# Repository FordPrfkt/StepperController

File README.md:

# StepperController
Stepper Motor Controller using TMC2660

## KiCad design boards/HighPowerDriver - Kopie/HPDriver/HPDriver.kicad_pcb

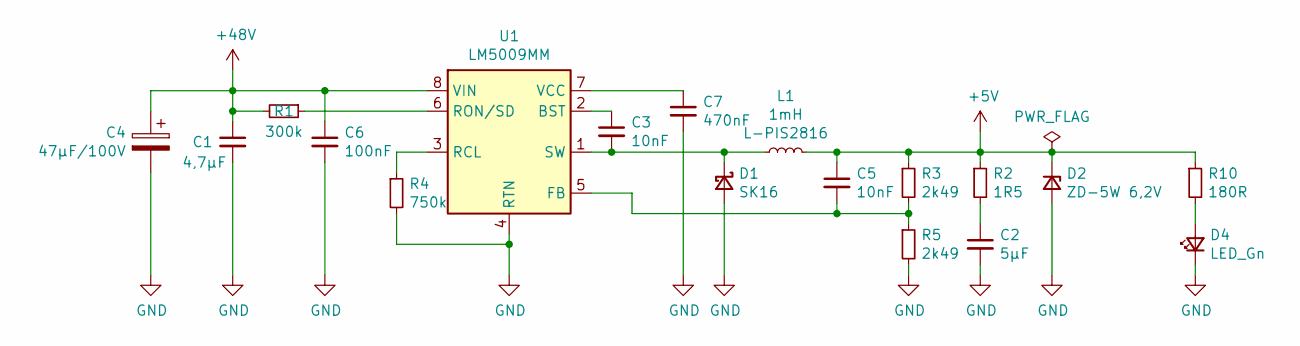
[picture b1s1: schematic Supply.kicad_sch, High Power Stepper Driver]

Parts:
C1: 4,7µF; C_1210_3225Metric
C2: 5µF; C_1210_3225Metric
C3, C5: 10nF; C_0805_2012Metric
C4: 47µF/100V; CP_Elec_8x10
C6: 100nF; C_0805_2012Metric
C7: 470nF; C_0805_2012Metric
D1: SK16; D_SMA
D2: ZD-5W 6,2V; D_SMB
D4: LED_Gn; LED_0805_2012Metric
L1: 1mH; L_7.3x7.3_H4.5
R1: 300k; R_0805_2012Metric
R2: 1R5; R_0805_2012Metric
R3, R5: 2k49; R_0805_2012Metric
R4: 750k; R_0805_2012Metric
R10: 180R; R_0805_2012Metric
U1: LM5009MM; MSOP-8_3x3mm_P0.65mm

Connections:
+5V: C5.1, D2.1 (K), L1.2, R2.1, R3.1, R10.1; also elsewhere on the board
+48V: C1.1, C4.1, C6.1, R1.2, U1.8 (VIN); also elsewhere on the board
GND: C1.2, C2.2, C4.2, C6.2, C7.2, D1.2 (A), D2.2 (A), D4.1 (K), R4.2, R5.2, U1.4 (RTN); also elsewhere on the board
unnamed: C2.1, R2.2
unnamed: C3.1, U1.2 (BST)
unnamed: C3.2, D1.1 (K), L1.1, U1.1 (SW)
unnamed: C5.2, R3.2, R5.1, U1.5 (FB)
unnamed: C7.1, U1.7 (VCC)
unnamed: D4.2 (A), R10.2
unnamed: R1.1, U1.6 (RON/SD)
unnamed: R4.1, U1.3 (RCL)

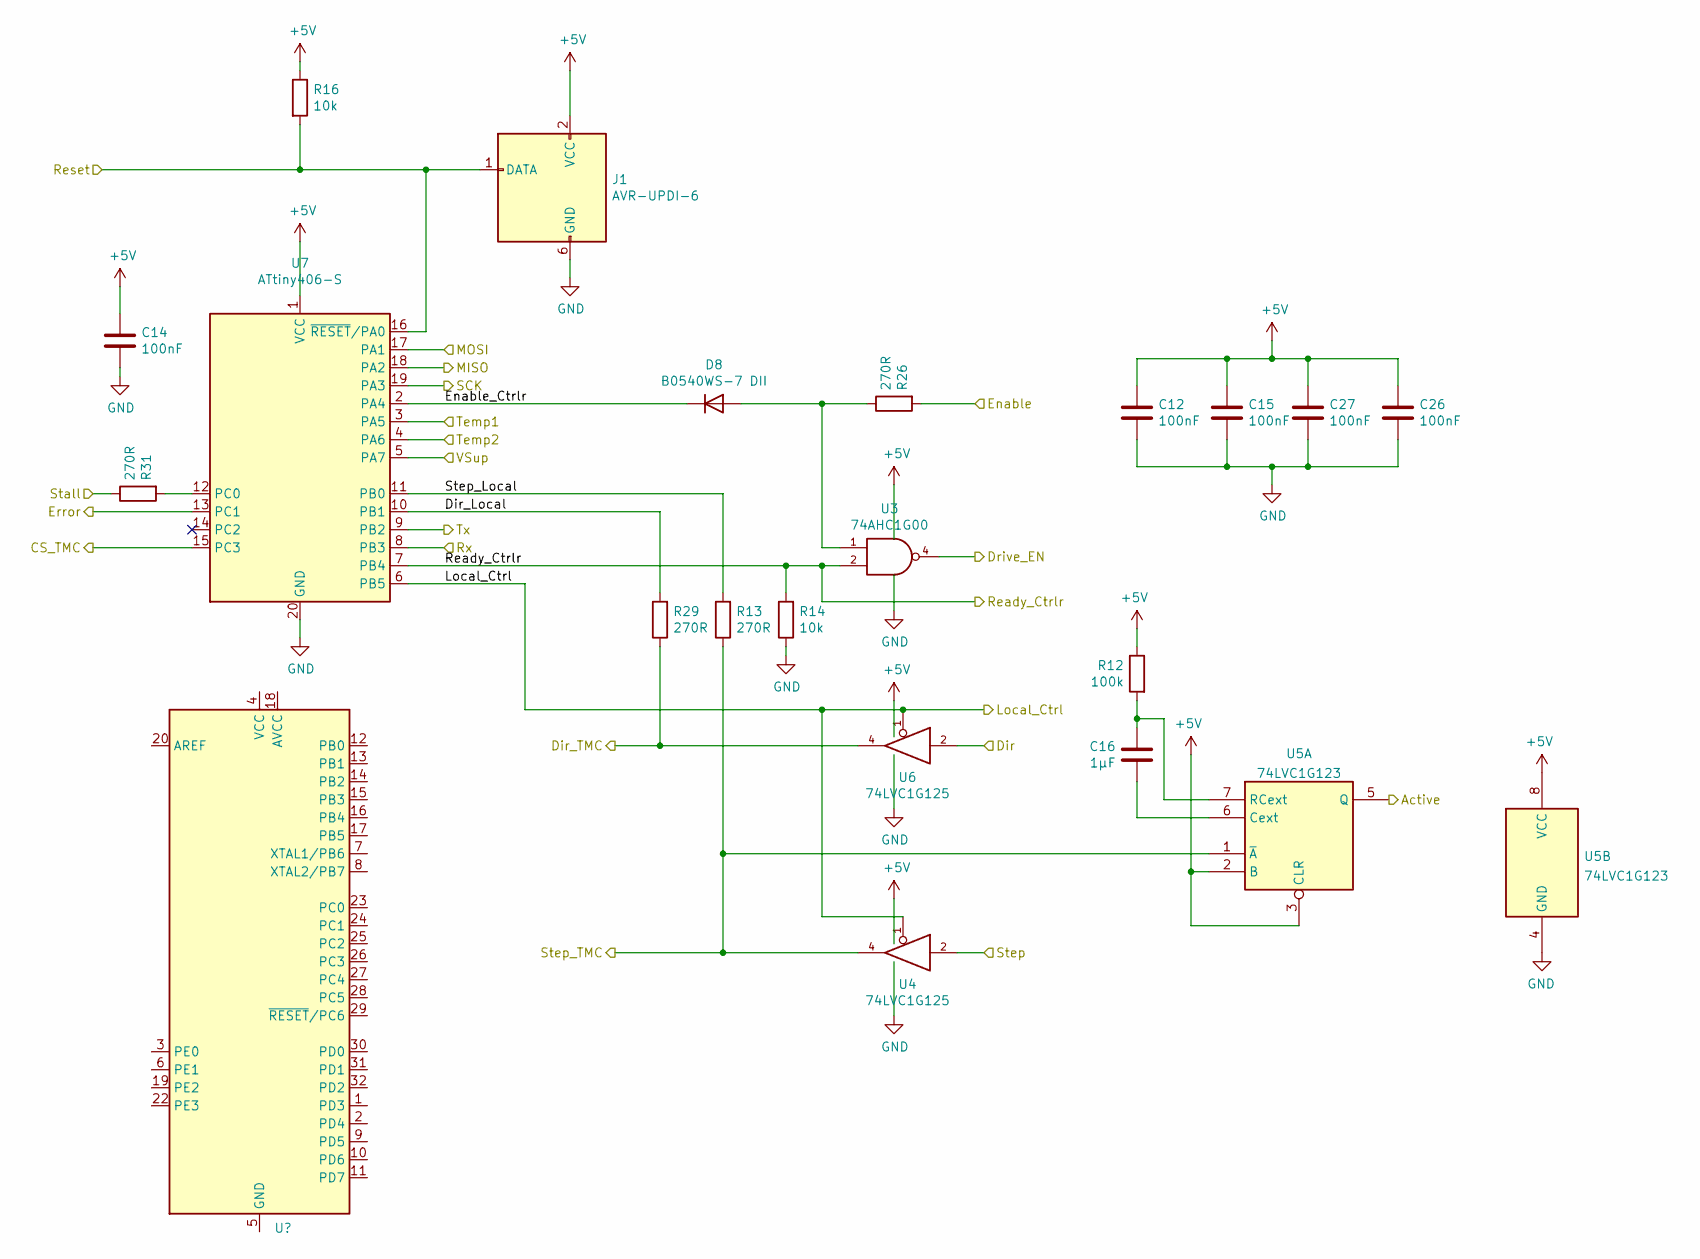
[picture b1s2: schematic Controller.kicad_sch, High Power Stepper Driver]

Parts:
C12, C14, C15, C26, C27: 100nF; C_0805_2012Metric
C16: 1µF; C_0805_2012Metric
D8: B0540WS-7 DII; D_SOD-323
J1: AVR-UPDI-6; IDC-Header_2x03_P2.54mm_Vertical
R12: 100k; R_0805_2012Metric
R13, R26, R29, R31: 270R; R_0805_2012Metric
R14, R16: 10k; R_0805_2012Metric
U3: 74AHC1G00; SOT-23-5
U4, U6: 74LVC1G125; SOT-23-5
U5: 74LVC1G123; VSSOP-8_3.0x3.0mm_P0.65mm
U7: ATtiny406-S; SOIC-20W_7.5x12.8mm_P1.27mm

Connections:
+5V: C12.1, C14.1, C15.1, C26.1, C27.1, J1.2 (VCC), R12.1, R16.1, U3.5 (VCC), U4.5 (VCC), U5.2 (B), U5.3 (CLR), U5.8 (VCC), U6.5 (VCC), U7.1 (VCC); also elsewhere on the board
/Connector/Active: U5.5 (Q); also elsewhere on the board
/Connector/Dir: U6.2; also elsewhere on the board
/Connector/Enable: R26.2; also elsewhere on the board
/Connector/Error: U7.13 (PC1); also elsewhere on the board
/Connector/Reset: J1.1 (DATA), R16.2, U7.16 (~RESET/PA0); also elsewhere on the board
/Connector/Rx: U7.8 (PB3); also elsewhere on the board
/Connector/Stall: R31.1; also elsewhere on the board
/Connector/Step: U4.2; also elsewhere on the board
/Connector/Tx: U7.9 (PB2); also elsewhere on the board
/Connector/VSup: U7.5 (PA7); also elsewhere on the board
/Controller/CS_TMC: U7.15 (PC3); also elsewhere on the board
/Controller/Dir_Local: R29.2, U7.10 (PB1)
/Controller/Dir_TMC: R29.1, U6.4; also elsewhere on the board
/Controller/Drive_EN: U3.4; also elsewhere on the board
/Controller/Enable_Ctrlr: D8.1 (K), U7.2 (PA4)
/Controller/Local_Ctrl: U4.1, U6.1, U7.6 (PB5); also elsewhere on the board
/Controller/MISO: U7.18 (PA2); also elsewhere on the board
/Controller/MOSI: U7.17 (PA1); also elsewhere on the board
/Controller/Ready_Ctrlr: R14.2, U3.2, U7.7 (PB4); also elsewhere on the board
/Controller/SCK: U7.19 (PA3); also elsewhere on the board
/Controller/Step_Local: R13.2, U7.11 (PB0)
/Controller/Step_TMC: R13.1, U4.4, U5.1 (~A); also elsewhere on the board
/Controller/Temp1: U7.3 (PA5); also elsewhere on the board
/Controller/Temp2: U7.4 (PA6); also elsewhere on the board
GND: C12.2, C14.2, C15.2, C26.2, C27.2, J1.6 (GND), R14.1, U3.3 (GND), U4.3 (GND), U5.4 (GND), U6.3 (GND), U7.20 (GND); also elsewhere on the board
unnamed: C16.1, U5.6 (Cext)
unnamed: C16.2, R12.2, U5.7 (RCext)
unnamed: D8.2 (A), R26.1, U3.1
unnamed: R31.2, U7.12 (PC0)

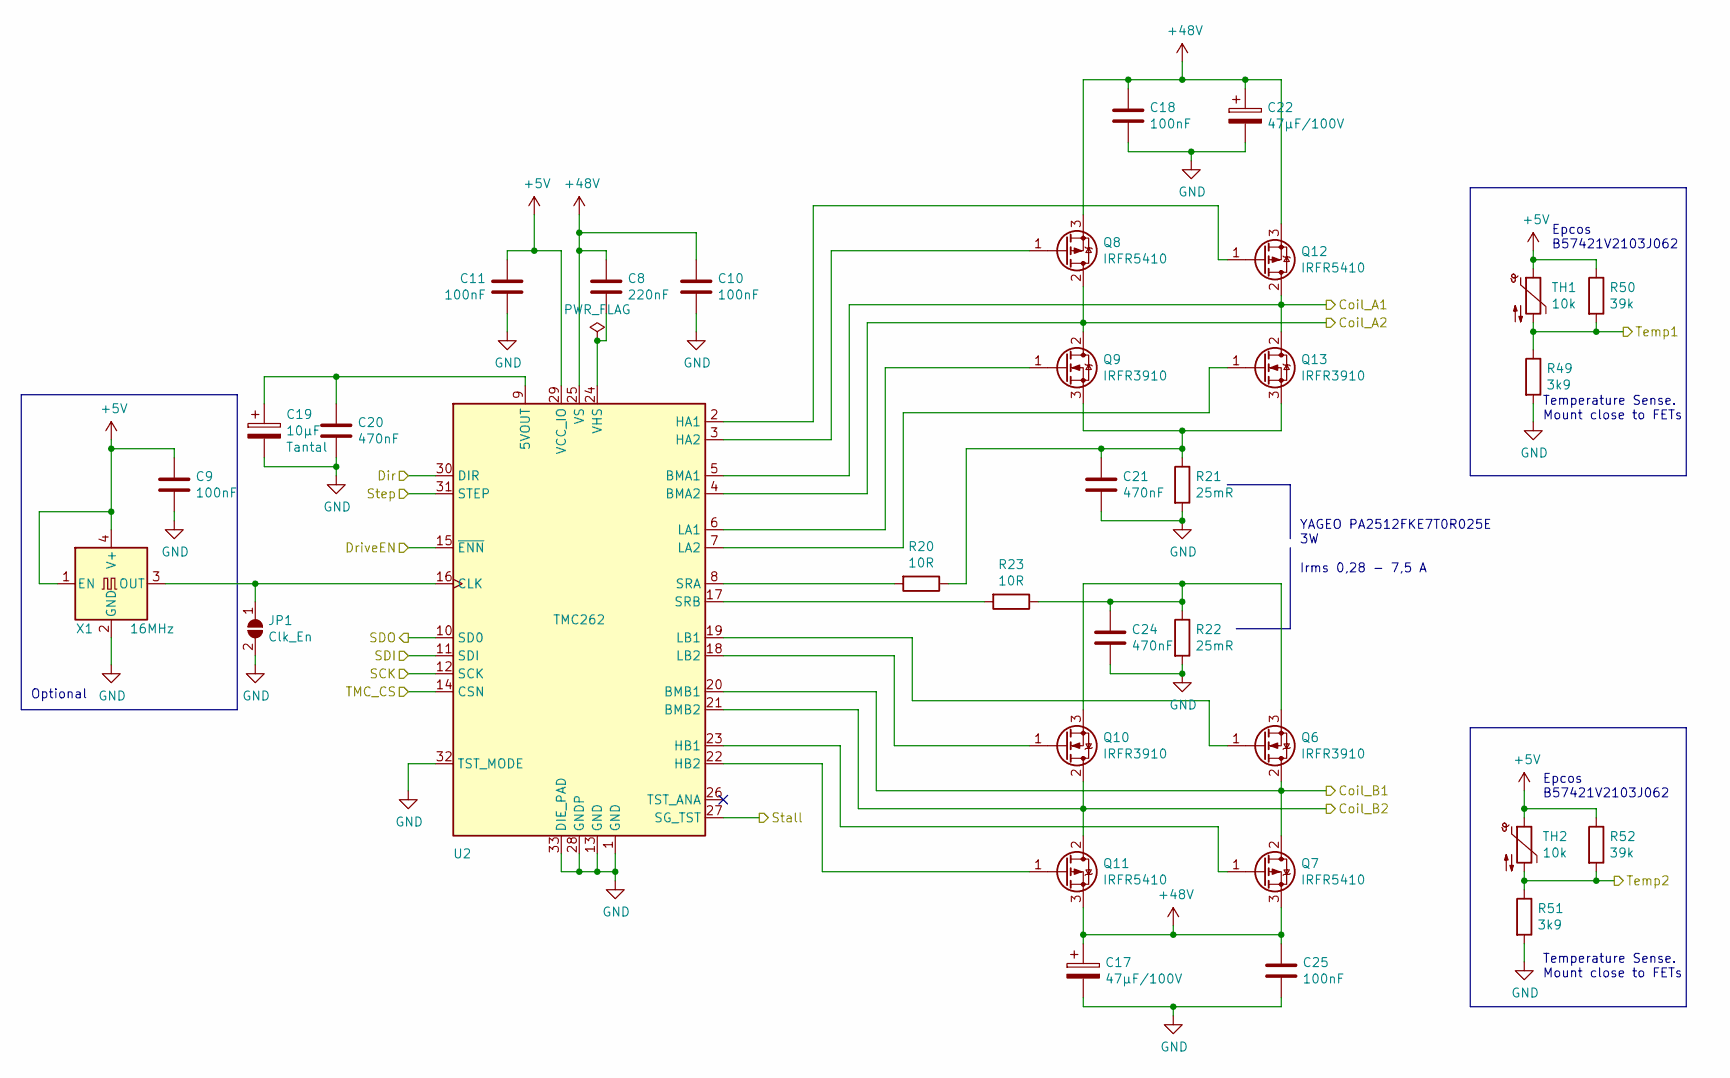
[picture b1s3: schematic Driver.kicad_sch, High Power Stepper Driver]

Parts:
C8: 220nF; C_0805_2012Metric
C9, C10, C11, C18, C25: 100nF; C_0805_2012Metric
C17, C22: 47µF/100V; CP_Elec_10x10
C19: 10µF; CP_EIA-3528-21_Kemet-B
C20, C21, C24: 470nF; C_0805_2012Metric
JP1: Clk_En; SolderJumper-2_P1.3mm_Open_TrianglePad1.0x1.5mm
Q6, Q9, Q10, Q13: IRFR3910; TO-252-2
Q7, Q8, Q11, Q12: IRFR5410; TO-252-2
R20, R23: 10R; R_0805_2012Metric
R21, R22: 25mR; R_2512_6332Metric
R49, R51: 3k9; R_0805_2012Metric
R50, R52: 39k; R_0805_2012Metric
TH1, TH2: 10k; R_0805_2012Metric
U2: TMC262; QFN-32-1EP_5x5mm_P0.5mm_EP3.45x3.45mm
X1: 16MHz; Oscillator_SMD_EuroQuartz_XO53-4Pin_5.0x3.2mm_HandSoldering

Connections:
+5V: C9.1, C11.1, R50.1, R52.1, TH1.1, TH2.1, U2.29 (VCC_IO), X1.1 (EN), X1.4 (V+); also elsewhere on the board
+48V: C8.1, C10.1, C17.1, C18.1, C22.1, C25.1, Q7.3 (S), Q8.3 (S), Q11.3 (S), Q12.3 (S), U2.25 (VS); also elsewhere on the board
/Connector/Coil_A1: Q12.2 (D), Q13.2 (D), U2.5 (BMA1); also elsewhere on the board
/Connector/Coil_A2: Q8.2 (D), Q9.2 (D), U2.4 (BMA2); also elsewhere on the board
/Connector/Coil_B1: Q6.2 (D), Q7.2 (D), U2.20 (BMB1); also elsewhere on the board
/Connector/Coil_B2: Q10.2 (D), Q11.2 (D), U2.21 (BMB2); also elsewhere on the board
/Connector/Stall: U2.27 (SG_TST); also elsewhere on the board
/Controller/CS_TMC: U2.14 (CSN); also elsewhere on the board
/Controller/Dir_TMC: U2.30 (DIR); also elsewhere on the board
/Controller/Drive_EN: U2.15 (~ENN); also elsewhere on the board
/Controller/MISO: U2.11 (SDI); also elsewhere on the board
/Controller/MOSI: U2.10 (SD0); also elsewhere on the board
/Controller/SCK: U2.12 (SCK); also elsewhere on the board
/Controller/Step_TMC: U2.31 (STEP); also elsewhere on the board
/Controller/Temp1: R49.1, R50.2, TH1.2; also elsewhere on the board
/Controller/Temp2: R51.1, R52.2, TH2.2; also elsewhere on the board
GND: C9.2, C10.2, C11.2, C17.2, C18.2, C19.2, C20.2, C21.2, C22.2, C24.2, C25.2, JP1.2 (B), R21.2, R22.2, R49.2, R51.2, U2.1 (GND), U2.13 (GND), U2.28 (GNDP), U2.32 (TST_MODE), U2.33 (DIE_PAD), X1.2 (GND); also elsewhere on the board
unnamed: C8.2, U2.24 (VHS)
unnamed: C19.1, C20.1, U2.9 (5VOUT)
unnamed: C21.1, Q9.3 (S), Q13.3 (S), R20.1, R21.1
unnamed: C24.1, Q6.3 (S), Q10.3 (S), R22.1, R23.1
unnamed: JP1.1 (A), U2.16 (CLK), X1.3 (OUT)
unnamed: Q6.1 (G), U2.19 (LB1)
unnamed: Q7.1 (G), U2.23 (HB1)
unnamed: Q8.1 (G), U2.3 (HA2)
unnamed: Q9.1 (G), U2.6 (LA1)
unnamed: Q10.1 (G), U2.18 (LB2)
unnamed: Q11.1 (G), U2.22 (HB2)
unnamed: Q12.1 (G), U2.2 (HA1)
unnamed: Q13.1 (G), U2.7 (LA2)
unnamed: R20.2, U2.8 (SRA)
unnamed: R23.2, U2.17 (SRB)

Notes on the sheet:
YAGEO PA2512FKE7T0R025E 3W Irms 0,28 - 7,5 A
Epcos B57421V2103J062
Temperature Sense. Mount close to FETs
Optional

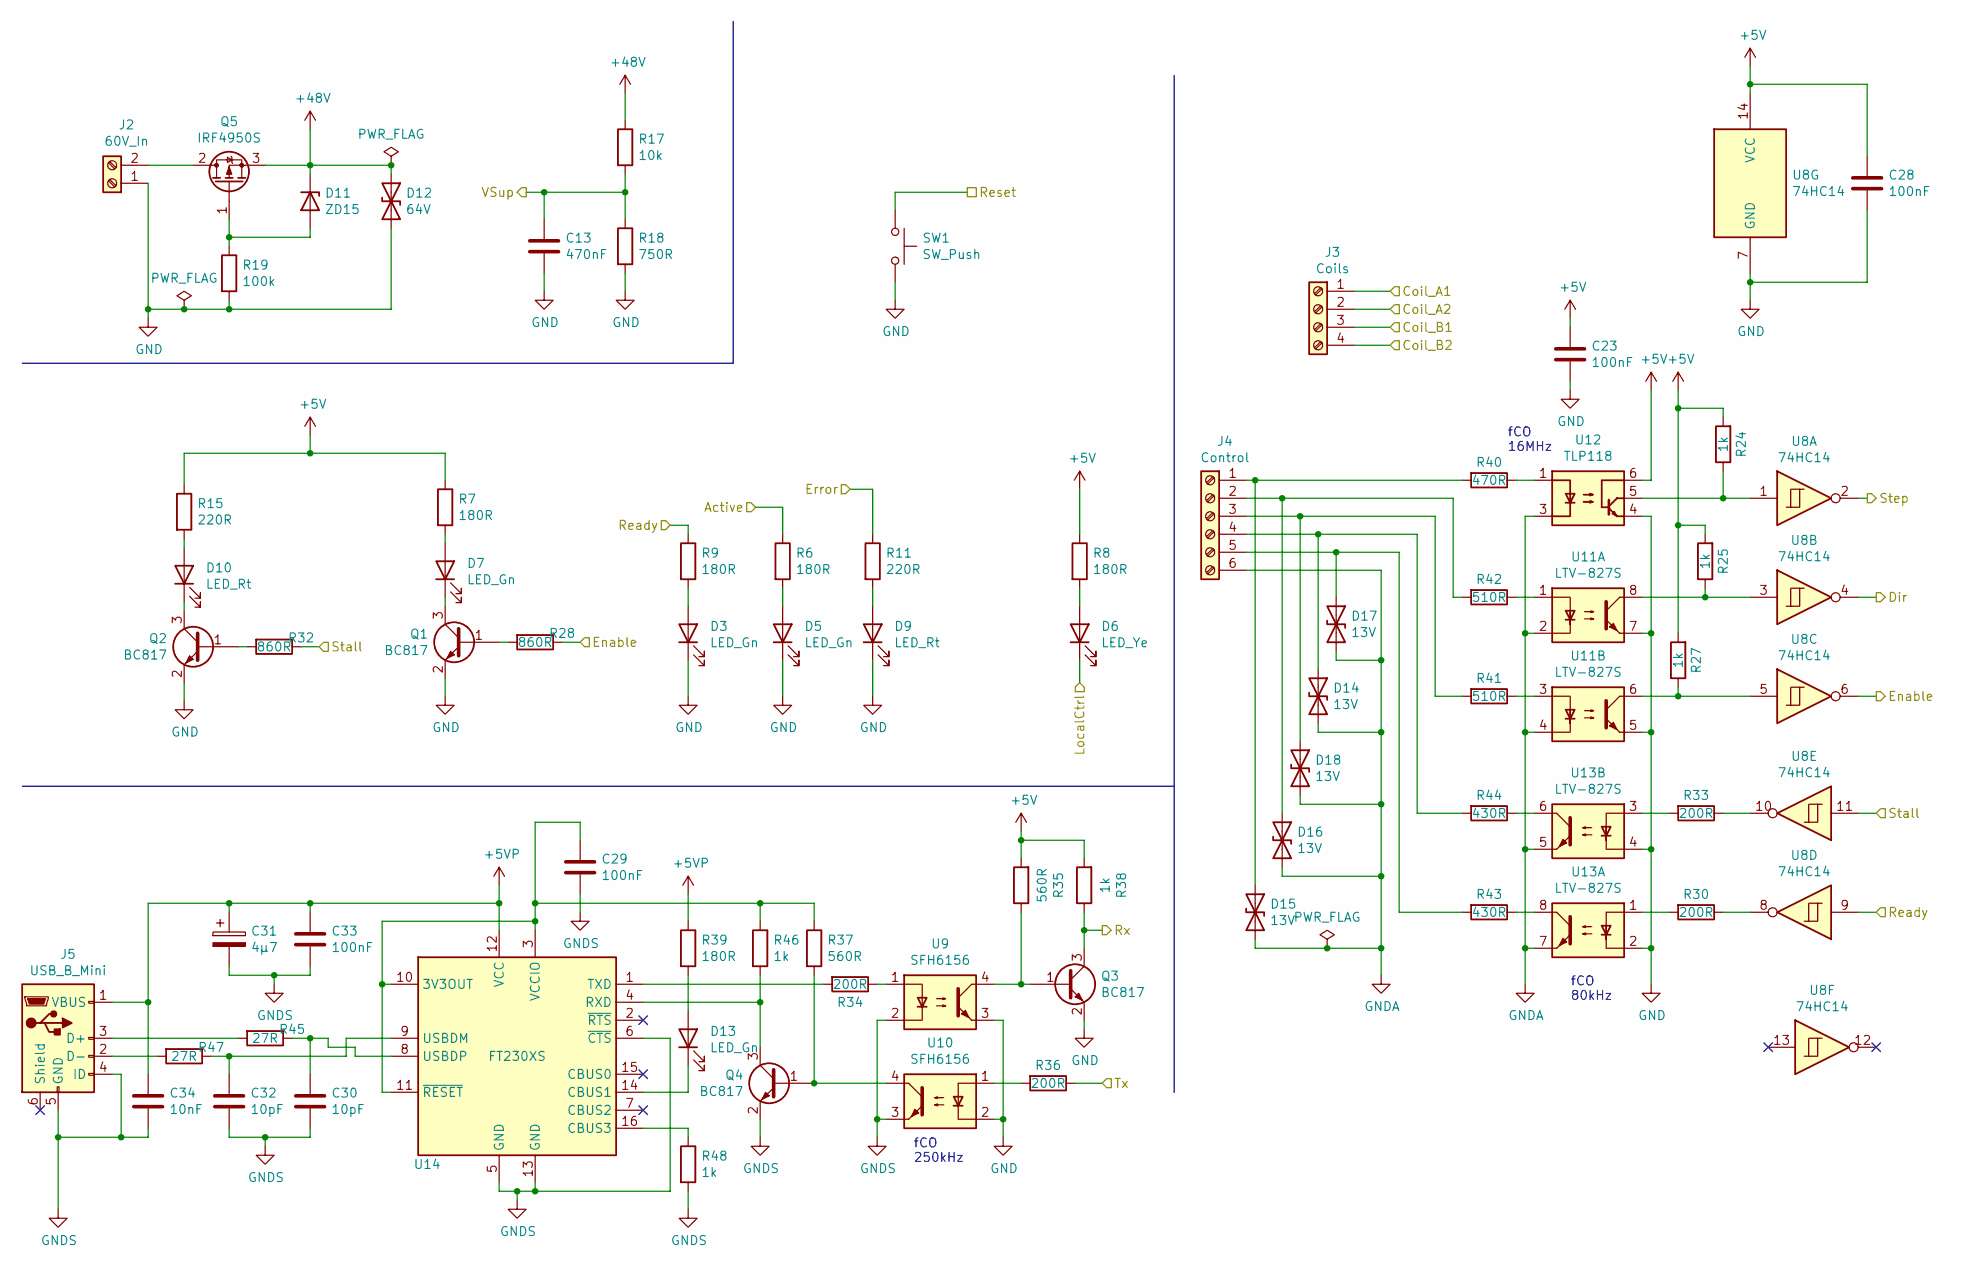
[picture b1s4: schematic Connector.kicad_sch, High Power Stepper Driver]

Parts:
C13: 470nF; C_0805_2012Metric
C23, C28, C29, C33: 100nF; C_0805_2012Metric
C30, C32: 10pF; C_0805_2012Metric
C31: 4µ7; C_0805_2012Metric_Pad1.15x1.40mm_HandSolder
C34: 10nF; C_0805_2012Metric
D3, D5, D7, D13: LED_Gn; LED_0805_2012Metric
D6: LED_Ye; LED_0805_2012Metric
D9, D10: LED_Rt; LED_0805_2012Metric
D11: ZD15; D_SOT-23_ANK
D12: 64V; D_SMB
D14, D15, D16, D17, D18: 13V; D_SMA
J2: 60V_In; PhoenixContact_MSTBA_2,5_2-G_1x02_P5.00mm_Horizontal
J3: Coils; PhoenixContact_MSTBA_2,5_4-G_1x04_P5.00mm_Horizontal
J4: Control; PhoenixContact_MSTBA_2,5_6-G_1x06_P5.00mm_Horizontal
J5: USB_B_Mini; USB_Mini-B_Lumberg_2486_01_Horizontal
Q1, Q2, Q3, Q4: BC817; SOT-23
Q5: IRF4950S; TO-263-2
R6, R7, R8, R9, R39: 180R; R_0805_2012Metric
R11, R15: 220R; R_0805_2012Metric
R17: 10k; R_0805_2012Metric
R18: 750R; R_0805_2012Metric
R19: 100k; R_0805_2012Metric
R24, R25, R27, R38, R46, R48: 1k; R_0805_2012Metric
R28, R32: 860R; R_0805_2012Metric
R30, R33, R34, R36: 200R; R_0805_2012Metric
R35, R37: 560R; R_0805_2012Metric
R40: 470R; R_0805_2012Metric
R41, R42: 510R; R_0805_2012Metric
R43, R44: 430R; R_0805_2012Metric
R45, R47: 27R; R_0805_2012Metric
SW1: SW_Push; SW_SPST_B3S-1000
U8: 74HC14; SOIC-14_3.9x8.7mm_P1.27mm
U9, U10: SFH6156; SMDIP-4_W7.62mm
U11, U13: LTV-827S; SMDIP-8_W9.53mm
U12: TLP118; MFSOP6-5_4.4x3.6mm_P1.27mm
U14: FT230XS; SSOP-16_3.9x4.9mm_P0.635mm

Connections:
+5V: C23.1, C28.1, R7.1, R8.1, R15.1, R24.2, R25.2, R27.2, R35.2, R38.2, U8.14 (VCC), U12.6; also elsewhere on the board
+5VP: C31.1, C33.1, C34.1, J5.1 (VBUS), R39.1, U14.12 (VCC)
+48V: D11.1 (K), D12.1 (A1), Q5.3 (S), R17.1; also elsewhere on the board
/Connector/Active: R6.1; also elsewhere on the board
/Connector/Coil_A1: J3.1; also elsewhere on the board
/Connector/Coil_A2: J3.2; also elsewhere on the board
/Connector/Coil_B1: J3.3; also elsewhere on the board
/Connector/Coil_B2: J3.4; also elsewhere on the board
/Connector/Dir: U8.4; also elsewhere on the board
/Connector/Enable: R28.1, U8.6; also elsewhere on the board
/Connector/Error: R11.1; also elsewhere on the board
/Connector/Reset: SW1.1; also elsewhere on the board
/Connector/Rx: Q3.3 (C), R38.1; also elsewhere on the board
/Connector/Stall: R32.1, U8.11; also elsewhere on the board
/Connector/Step: U8.2; also elsewhere on the board
/Connector/Tx: R36.1; also elsewhere on the board
/Connector/VSup: C13.1, R17.2, R18.1; also elsewhere on the board
/Controller/Local_Ctrl: D6.1 (K); also elsewhere on the board
/Controller/Ready_Ctrlr: R9.1, U8.9; also elsewhere on the board
GND: C13.2, C23.2, C28.2, D3.1 (K), D5.1 (K), D9.1 (K), D12.2 (A2), J2.1, Q1.2 (E), Q2.2 (E), Q3.2 (E), R18.2, R19.2, SW1.2, U8.7 (GND), U9.3, U10.2, U11.5, U11.7, U12.4, U13.2, U13.4; also elsewhere on the board
GNDA: D14.2 (A2), D15.2 (A2), D16.2 (A2), D17.2 (A2), D18.2 (A2), J4.6, U11.2, U11.4, U12.3, U13.5, U13.7
GNDS: C29.2, C30.2, C31.2, C32.2, C33.2, C34.2, J5.4 (ID), J5.5 (GND), Q4.2 (E), R48.2, U9.2, U10.3, U14.5 (GND), U14.6 (~CTS), U14.13 (GND)
unnamed: C29.1, R37.1, R46.1, U14.3 (VCCIO), U14.10 (3V3OUT), U14.11 (~RESET)
unnamed: C30.1, R45.1, U14.8 (USBDP)
unnamed: C32.1, R47.1, U14.9 (USBDM)
unnamed: D3.2 (A), R9.2
unnamed: D5.2 (A), R6.2
unnamed: D6.2 (A), R8.2
unnamed: D7.1 (K), Q1.3 (C)
unnamed: D7.2 (A), R7.2
unnamed: D9.2 (A), R11.2
unnamed: D10.1 (K), Q2.3 (C)
unnamed: D10.2 (A), R15.2
unnamed: D11.2 (A), Q5.1 (G), R19.1
unnamed: D13.1 (K), U14.14 (CBUS1)
unnamed: D13.2 (A), R39.2
unnamed: D14.1 (A1), J4.4, R44.2
unnamed: D15.1 (A1), J4.1, R40.2
unnamed: D16.1 (A1), J4.2, R42.2
unnamed: D17.1 (A1), J4.5, R43.2
unnamed: D18.1 (A1), J4.3, R41.2
unnamed: J2.2, Q5.2 (D)
unnamed: J5.2 (D-), R47.2
unnamed: J5.3 (D+), R45.2
unnamed: Q1.1 (B), R28.2
unnamed: Q2.1 (B), R32.2
unnamed: Q3.1 (B), R35.1, U9.4
unnamed: Q4.1 (B), R37.2, U10.4
unnamed: Q4.3 (C), R46.2, U14.4 (RXD)
unnamed: R24.1, U8.1, U12.5
unnamed: R25.1, U8.3, U11.8
unnamed: R27.1, U8.5, U11.6
unnamed: R30.1, U8.8
unnamed: R30.2, U13.1
unnamed: R33.1, U8.10
unnamed: R33.2, U13.3
unnamed: R34.1, U9.1
unnamed: R34.2, U14.1 (TXD)
unnamed: R36.2, U10.1
unnamed: R40.1, U12.1
unnamed: R41.1, U11.3
unnamed: R42.1, U11.1
unnamed: R43.1, U13.8
unnamed: R44.1, U13.6
unnamed: R48.1, U14.16 (CBUS3)

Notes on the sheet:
fCO 80kHz
fCO 16MHz
fCO 250kHz

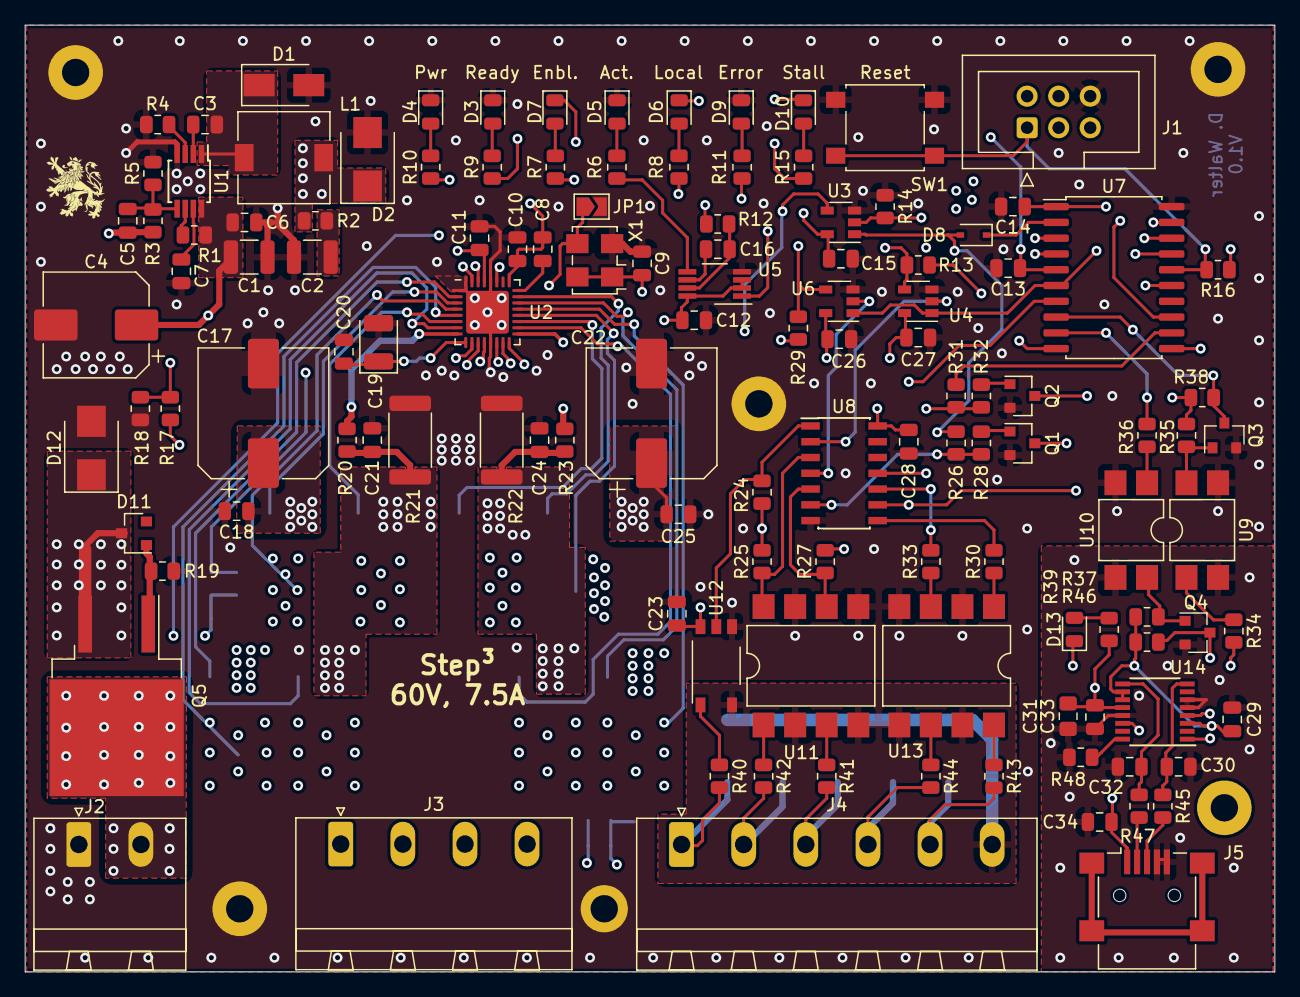
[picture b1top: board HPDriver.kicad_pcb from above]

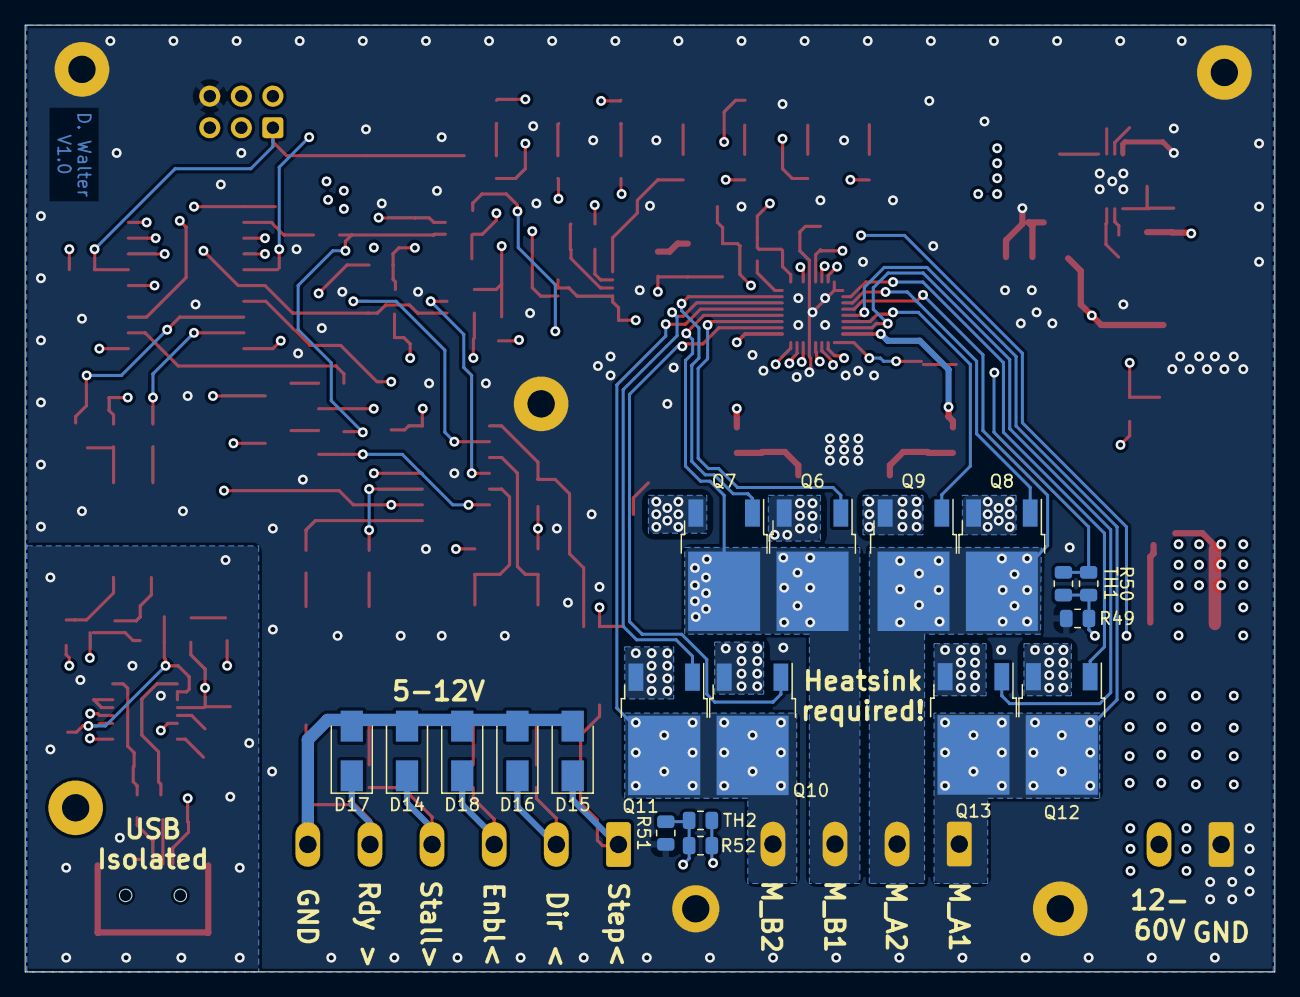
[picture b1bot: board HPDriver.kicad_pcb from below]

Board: 4 copper layers, 100.6 x 76.2 mm, 142 parts (19 on the bottom side), 104 nets.

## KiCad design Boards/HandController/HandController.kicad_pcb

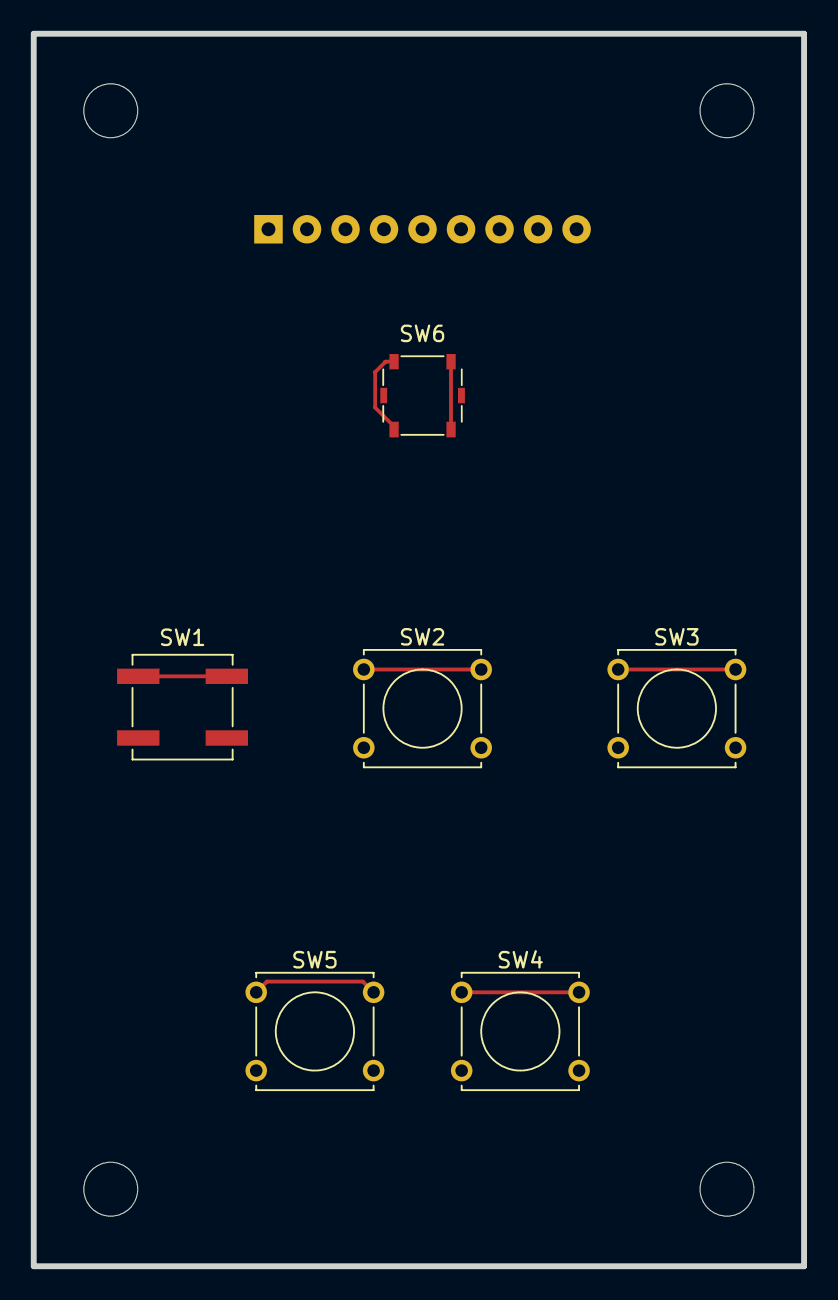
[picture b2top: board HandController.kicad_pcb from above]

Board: 2 copper layers, 50.0 x 80.0 mm, 7 parts (1 on the bottom side), 8 nets.

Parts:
J1: Conn_01x09; JST_EH_B09B-EH-A_09x2.50mm_Straight
SW1: SW_Push; SW_SPST_B3SL-1002P
SW2, SW3, SW4, SW5: SW_Push; SW_Tactile_Straight_KSA0Axx1LFTR
SW6: Rotary_Encoder; SW_SPST_Panasonic_EVQPL_3PL_5PL_PT_A08

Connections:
GND: J1.9, SW1.2, SW2.2, SW3.2, SW4.2, SW5.2
unnamed: J1.1, SW6.1
unnamed: J1.2, SW6.2
unnamed: J1.4, SW1.1
unnamed: J1.5, SW2.1
unnamed: J1.6, SW3.1
unnamed: J1.7, SW4.1
unnamed: J1.8, SW5.1
